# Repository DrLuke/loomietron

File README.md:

# loomietron
ESP8266-driven Electroluminescent driver

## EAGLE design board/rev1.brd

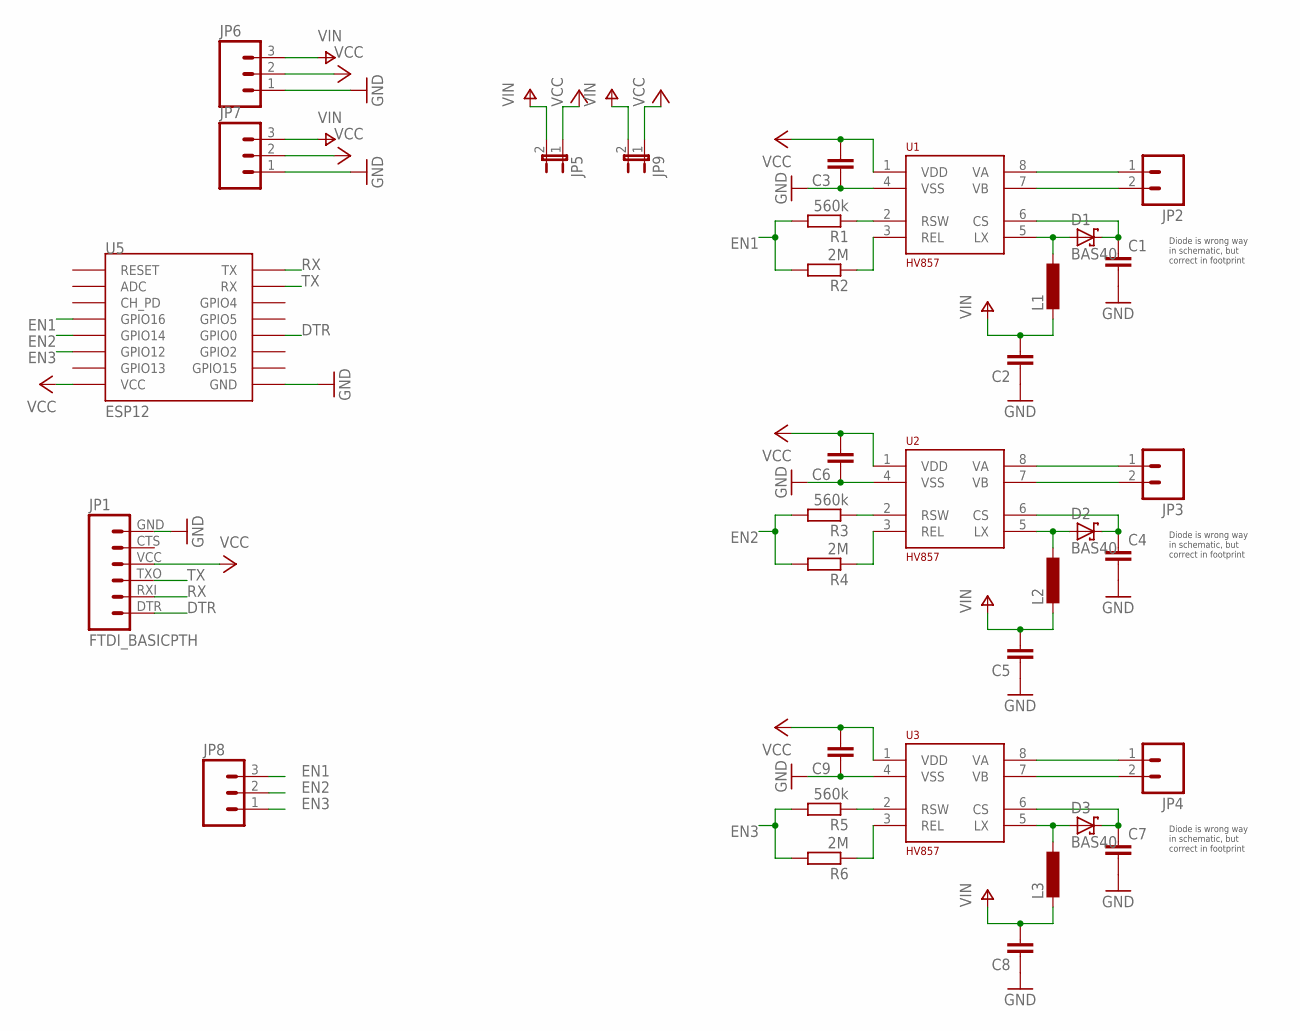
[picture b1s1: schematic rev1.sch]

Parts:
C1, C2, C3, C4, C5, C6, C7, C8, C9: C-EUC0603; C0603
D1, D2, D3: BAS40; SOT23
JP1: FTDI_BASICPTH; FTDI_BASIC
JP2, JP3, JP4: M02PTH; 1X02
JP5, JP9: JUMPER-2SMD-NC; SJ_2S
JP6, JP7, JP8: M03PTH; 1X03
L1, L2, L3: L-EUL3225M; L3225M
R1, R3, R5: 560k; R0603
R2, R4, R6: 2M; R0603
U1, U2, U3: HV857; MSOP8
U5: ESP12

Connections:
DTR: JP1.DTR (1), U5.GPIO0
EN1: JP8.3, R1.2, R2.2, U5.GPIO16
EN2: JP8.2, R3.2, R4.2, U5.GPIO14
EN3: JP8.1, R5.2, R6.2, U5.GPIO12
GND: C1.2, C2.1, C3.1, C4.2, C5.1, C6.1, C7.2, C8.1, C9.1, JP1.GND (6), JP6.1, JP7.1, U1.4 (VSS), U2.4 (VSS), U3.4 (VSS), U5.GND
unnamed: R1.1, U1.2 (RSW)
unnamed: R2.1, U1.3 (REL)
unnamed: R3.1, U2.2 (RSW)
unnamed: JP2.1, U1.8 (VA)
unnamed: JP2.2, U1.7 (VB)
unnamed: C1.1, D1.3 (C), U1.6 (CS)
unnamed: D1.1 (A), L1.1, U1.5 (LX)
unnamed: R4.1, U2.3 (REL)
unnamed: D2.1 (A), L2.1, U2.5 (LX)
unnamed: C4.1, D2.3 (C), U2.6 (CS)
unnamed: JP3.1, U2.8 (VA)
unnamed: JP3.2, U2.7 (VB)
unnamed: R5.1, U3.2 (RSW)
unnamed: R6.1, U3.3 (REL)
unnamed: D3.1 (A), L3.1, U3.5 (LX)
unnamed: C7.1, D3.3 (C), U3.6 (CS)
unnamed: JP4.1, U3.8 (VA)
unnamed: JP4.2, U3.7 (VB)
RX: JP1.RXI (2), U5.TX
TX: JP1.TXO (3), U5.RX
V+: C2.2, C5.2, C8.2, JP5.2, JP6.3, JP7.3, JP9.2, L1.2, L2.2, L3.2
VCC: C3.2, C6.2, C9.2, JP1.VCC (4), JP5.1, JP6.2, JP7.2, JP9.1, U1.1 (VDD), U2.1 (VDD), U3.1 (VDD), U5.VCC

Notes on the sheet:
Diode is wrong way in schematic, but correct in footprint

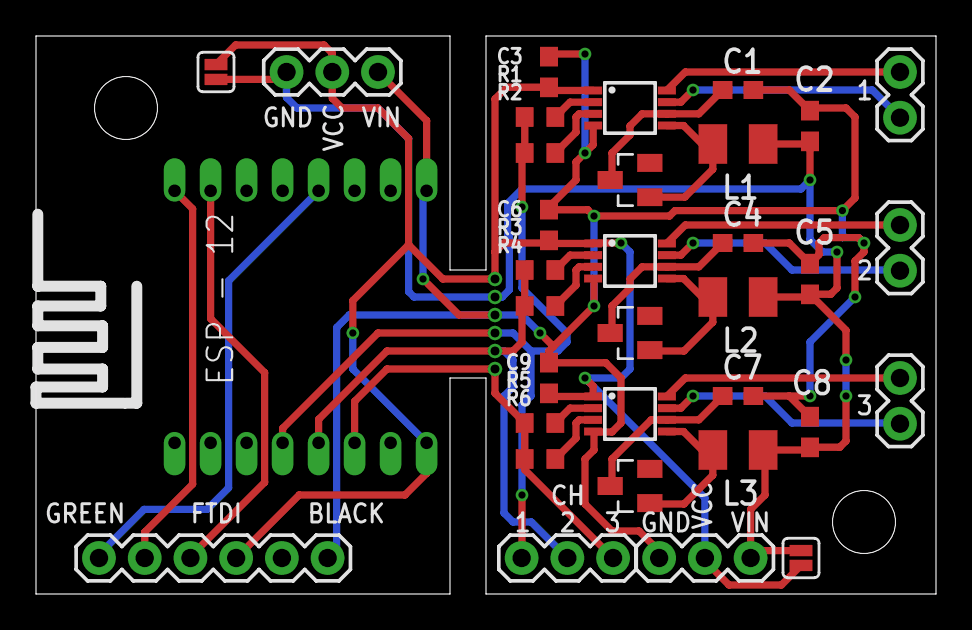
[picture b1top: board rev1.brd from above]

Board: 2 copper layers, 50.0 x 31.0 mm, 34 parts (0 on the bottom side), 27 nets.

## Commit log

2015-12-01 Rev1 of PCB (sent into prod)

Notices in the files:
parts and their libraries:
SparkFun: Licensing: CC v3.0 Share-Alike You are welcome to use this library for commercial purposes.
